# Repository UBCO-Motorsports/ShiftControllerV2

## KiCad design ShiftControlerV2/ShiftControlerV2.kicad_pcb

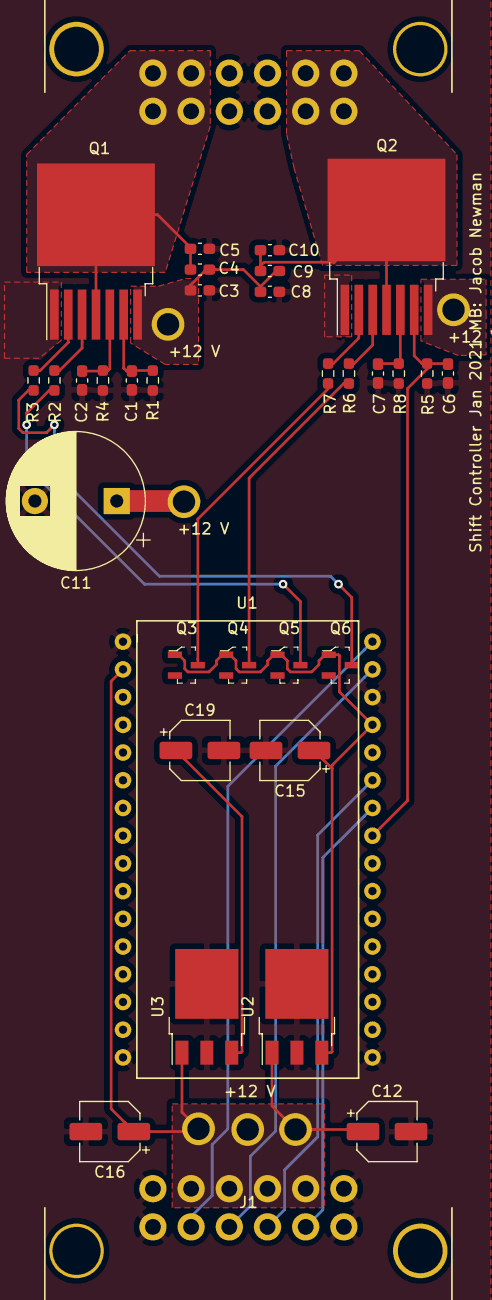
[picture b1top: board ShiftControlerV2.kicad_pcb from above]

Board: 2 copper layers, 40 parts (0 on the bottom side), 26 nets.

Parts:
 : 12_Gauge_TH
 #2: 12_Gauge_TH
+12 V, +12 V#2, +12 V#3, +12 V#4: 12_Gauge_TH
C1, C6: 1n; C_0603_1608Metric_Pad1.08x0.95mm_HandSolder
C2, C3, C7, C8: 100n; C_0603_1608Metric_Pad1.08x0.95mm_HandSolder
C4, C5, C9, C10: 220n; C_0603_1608Metric_Pad1.08x0.95mm_HandSolder
C11: 1000u; CP_Radial_D12.5mm_P7.50mm
C12, C15, C16, C19: 10u; CP_Elec_5x4.4
J1, J2: Conn_02x06_Counter_Clockwise; MX120G
Q1, Q2: BTN8982TA; TO-263-7_TabPin8
Q3, Q4, Q5, Q6: BSS138; SOT-23-3
R1, R5: 1k; R_0603_1608Metric_Pad0.98x0.95mm_HandSolder
R2, R3, R6, R7: 10k; R_0603_1608Metric_Pad0.98x0.95mm_HandSolder
R4, R8: 510; R_0603_1608Metric_Pad0.98x0.95mm_HandSolder
U1: ControllerBoardV2; Breadboard_Center_32pin
U2: LM1117-3.3; TO-252-3_TabPin4
U3: NCV7805BDTRKG; TO-252-3_TabPin4

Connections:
+3V3: C15.1, Q3.1, Q4.1, Q5.1, Q6.1, U1.20, U2.3
+5V: C19.1, U3.3
+12V: .1, #2.1, +12 V.1, +12 V#2.1, +12 V#3.1, +12 V#4.1, C3.2, C4.1, C8.2, C9.1, C11.1, C12.1, C16.1, J1.2, J1.3, J1.4, J1.5, Q1.7, Q2.7, U1.2, U2.1, U3.1
CANH: J1.9, U1.18
CANL: J1.8, U1.17
CURRENT1: C1.1, Q1.6, R1.1, U1.25
CURRENT2: C6.1, Q2.6, R5.1, U1.24
GND: C1.2, C2.2, C3.1, C5.2, C6.2, C7.2, C8.1, C10.2, C11.2, C12.2, C15.2, C16.2, C19.2, J1.1, J1.6, J1.7, J1.12, J2.3, J2.4, J2.9, J2.10, Q1.1, Q2.1, R1.2, R4.2, R5.2, R8.2, U1.1, U1.16, U1.19, U1.32, U2.2, U2.4, U3.2, U3.4
IN1H: Q6.3, R3.2
IN1L: Q3.2, U1.31
IN2H: Q3.3, R7.2
IN2L: Q4.2, U1.30
INH1H: Q5.3, R2.2
INH1L: Q6.2, U1.29
INH2H: Q4.3, R6.2
INH2L: Q5.2, U1.28
unnamed: C2.1, Q1.5, R4.1
unnamed: C7.1, Q2.5, R8.1
unnamed: Q1.2, R3.1
unnamed: Q1.3, R2.1
unnamed: Q2.2, R7.1
unnamed: Q2.3, R6.1
OUT1: C4.2, C5.1, J2.5, J2.6, J2.11, J2.12, Q1.4, Q1.8
OUT2: C9.2, C10.1, J2.1, J2.2, J2.7, J2.8, Q2.4, Q2.8
UARTRX: J1.10, U1.22
UARTTX: J1.11, U1.23

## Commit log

2020-11-21 KiCad Project added
    Bridge Schematics added
2020-11-22 Component value updates
2020-11-27 pcb detangled
2020-11-27 Schematic Revised
2020-11-28 PCB Revised, Con Added
2021-01-26 Teeny tiny resistors
2021-01-26 Rough Draft Finished
2021-01-26 First Review
2021-01-27 Design reviewed
2022-04-04 Added Code
2022-04-05 Refactored Code/Trying to fix functions
2022-04-08 Update to provide additional power to micro
